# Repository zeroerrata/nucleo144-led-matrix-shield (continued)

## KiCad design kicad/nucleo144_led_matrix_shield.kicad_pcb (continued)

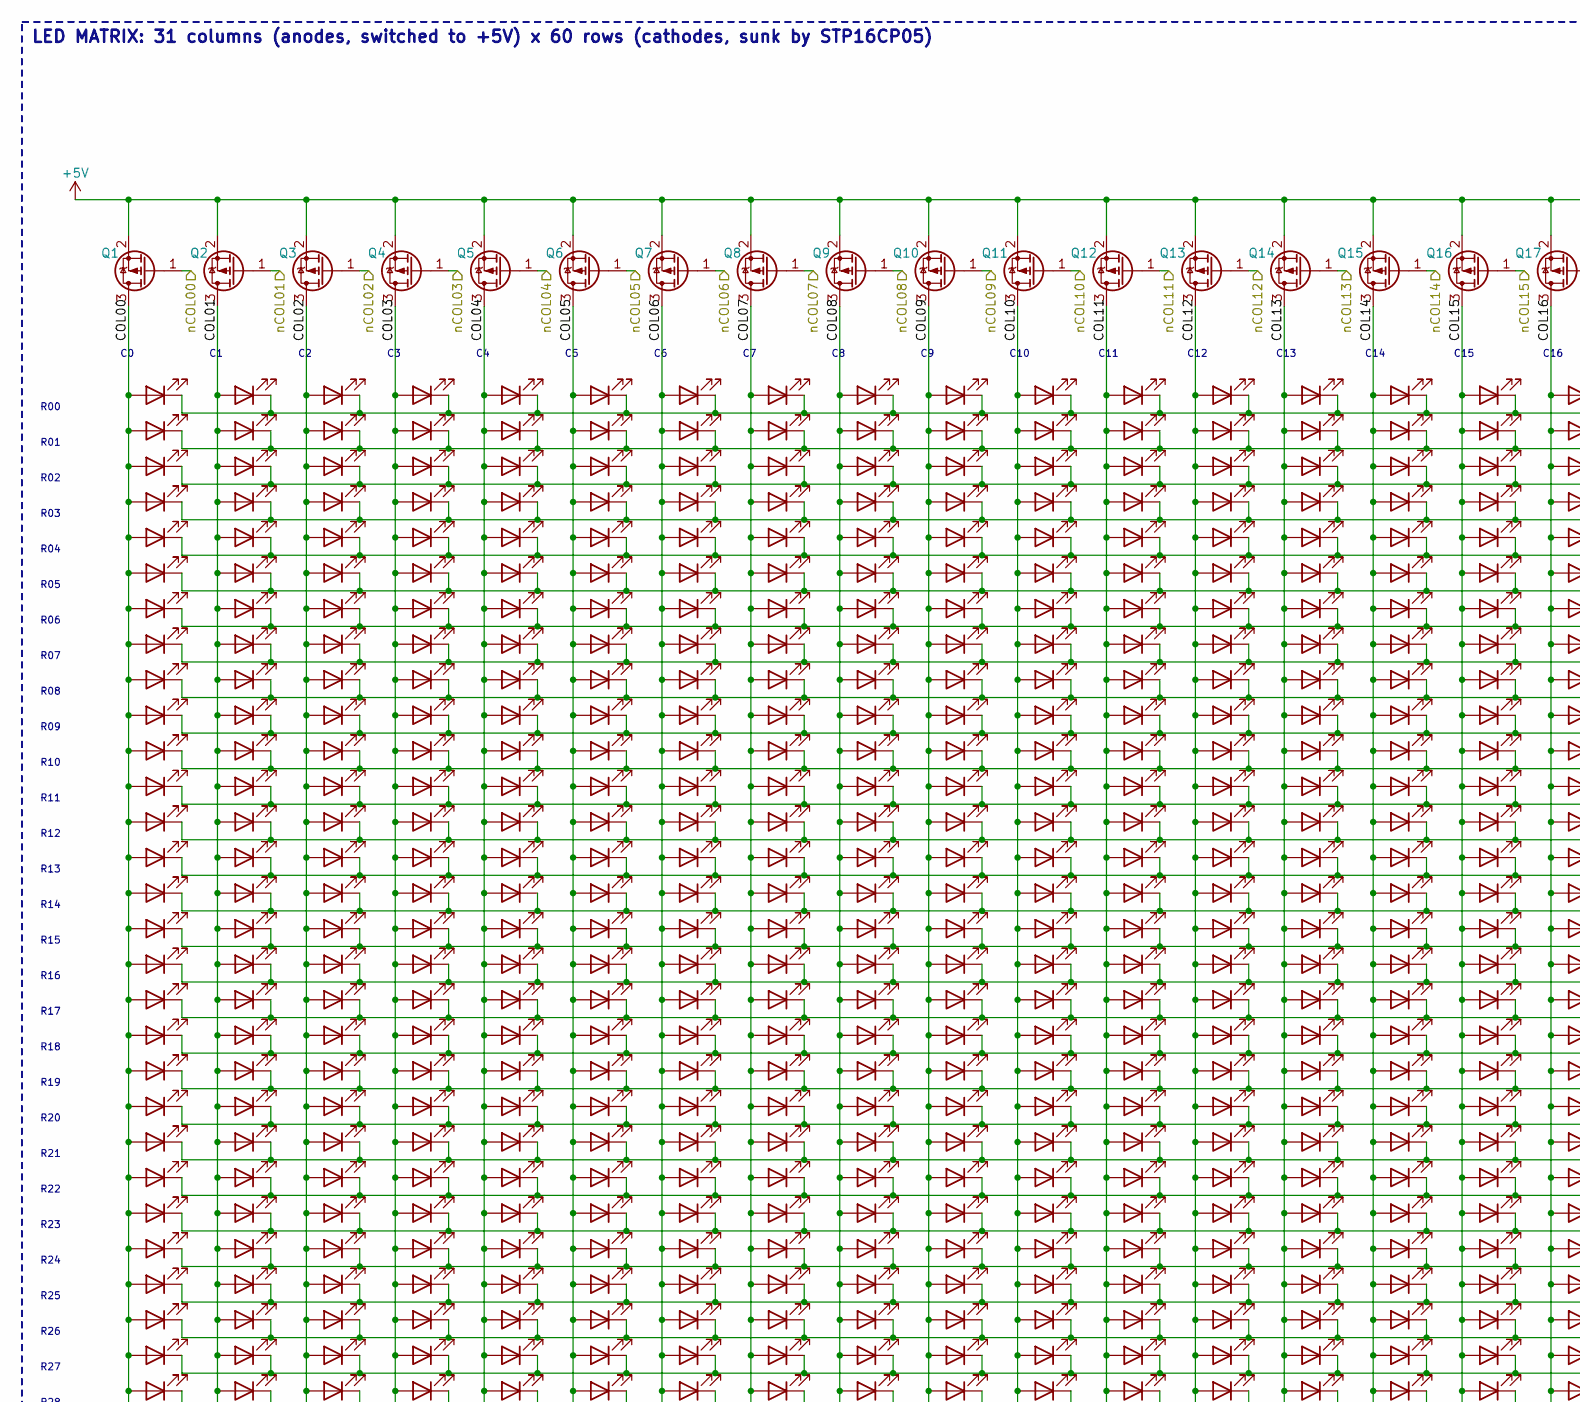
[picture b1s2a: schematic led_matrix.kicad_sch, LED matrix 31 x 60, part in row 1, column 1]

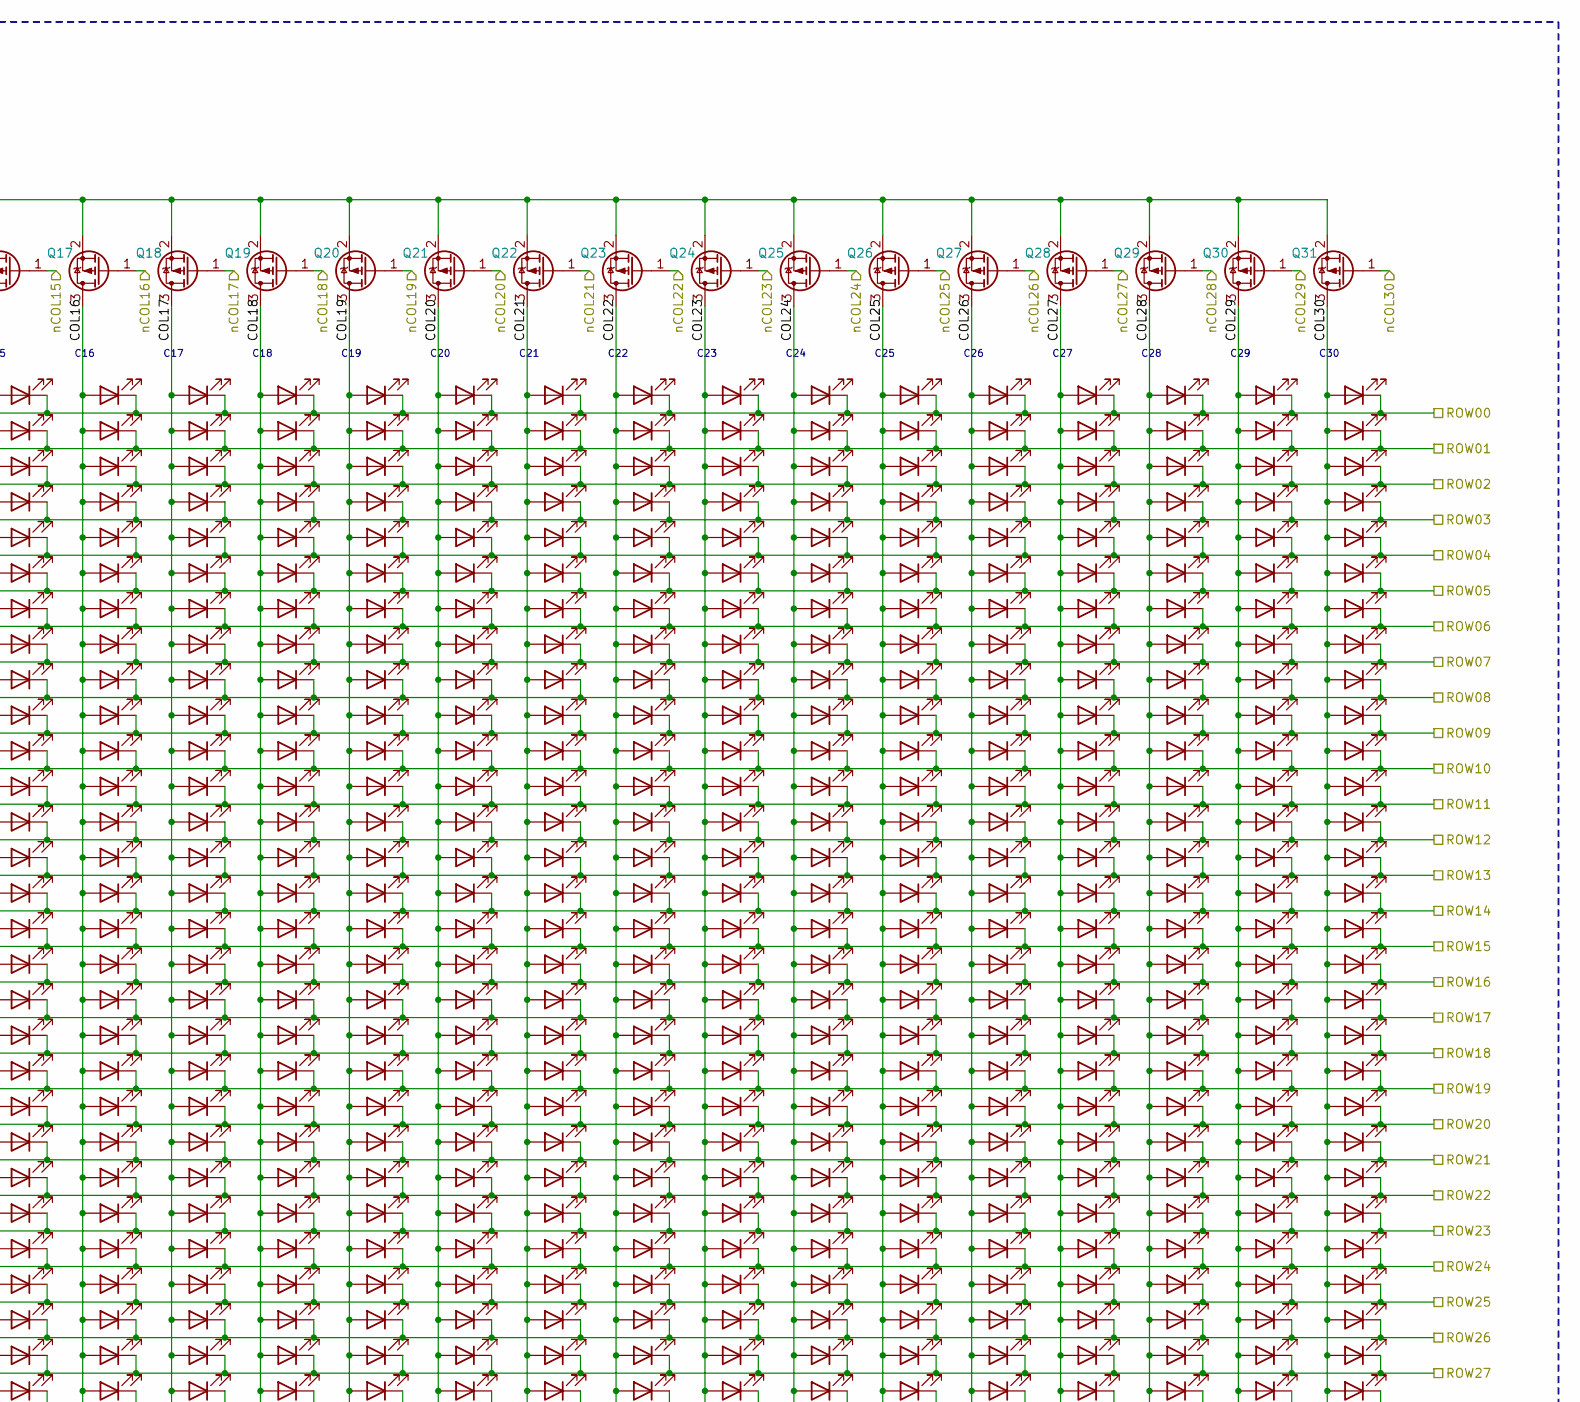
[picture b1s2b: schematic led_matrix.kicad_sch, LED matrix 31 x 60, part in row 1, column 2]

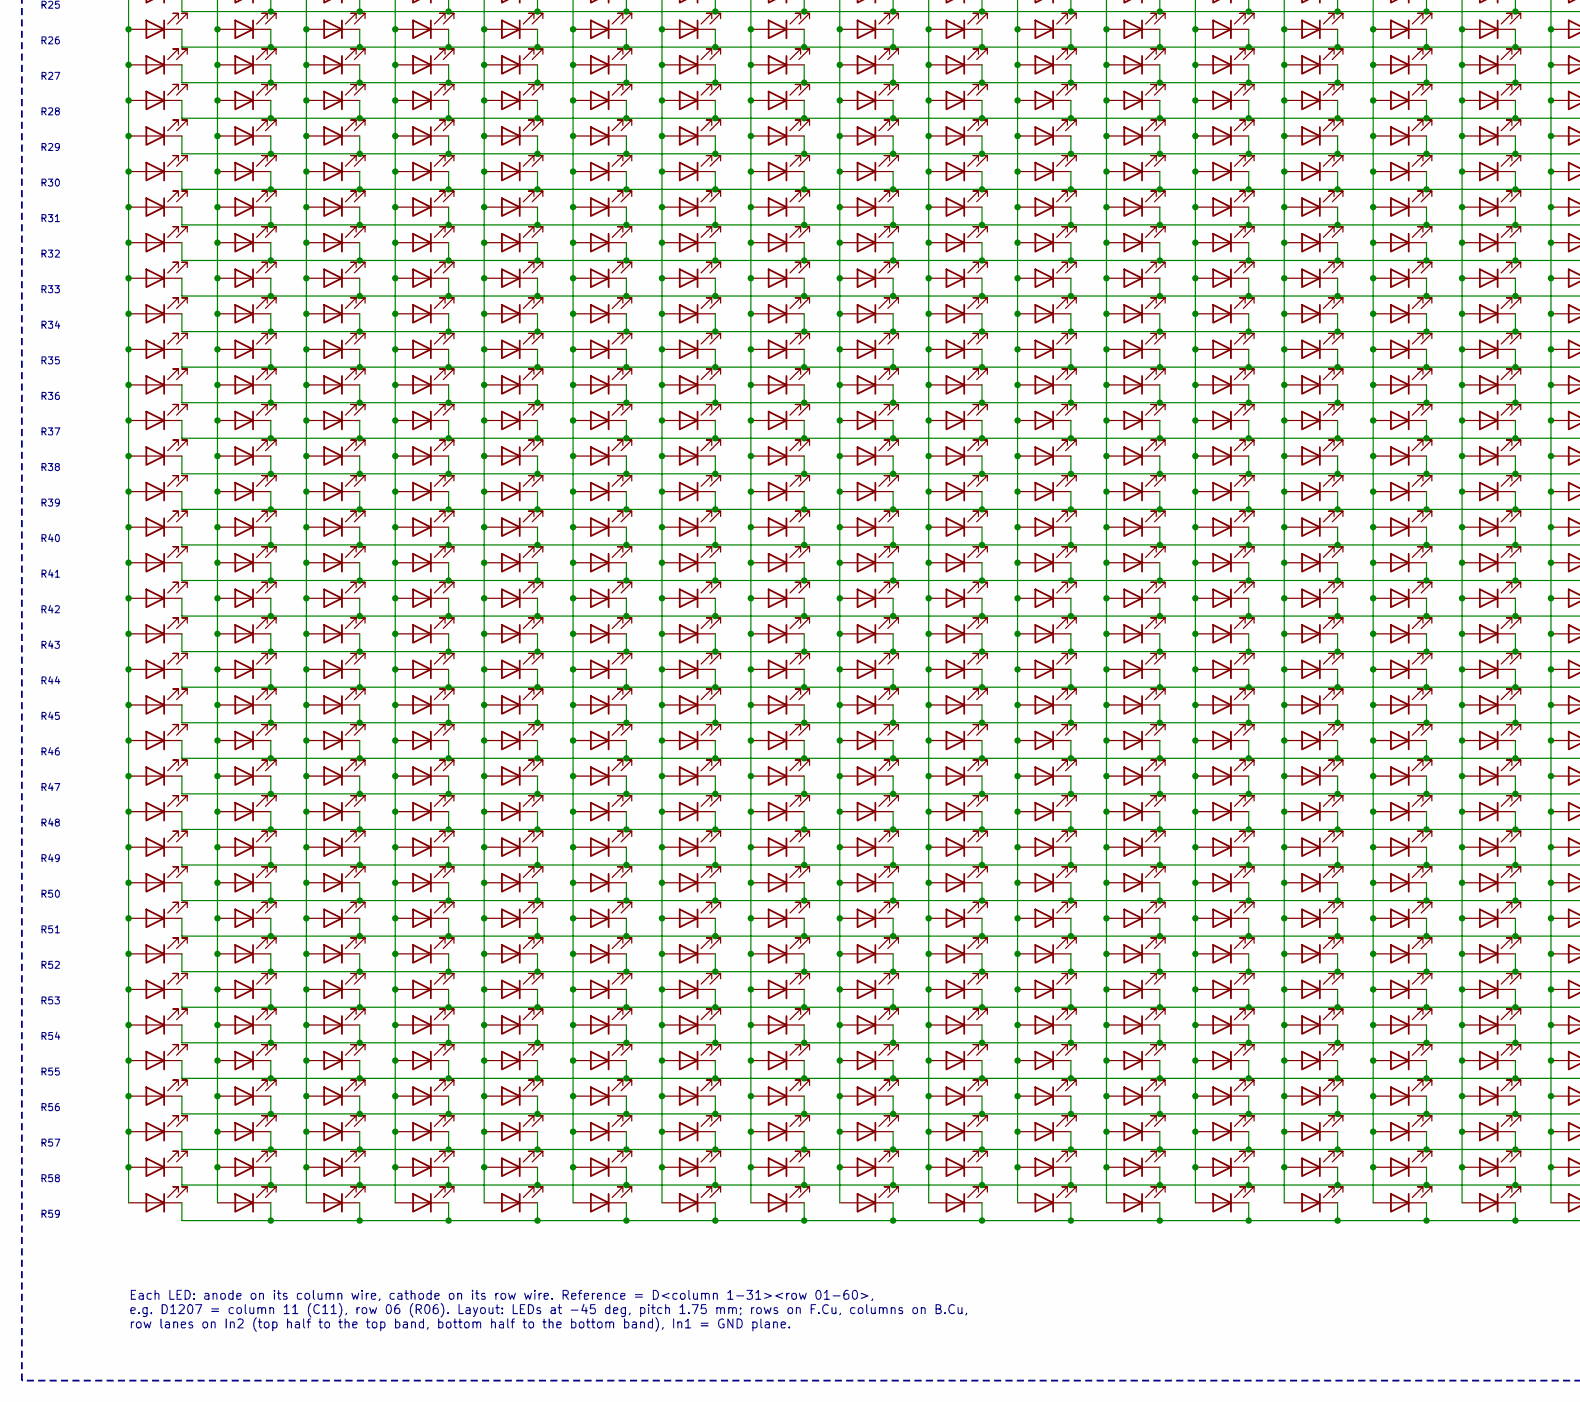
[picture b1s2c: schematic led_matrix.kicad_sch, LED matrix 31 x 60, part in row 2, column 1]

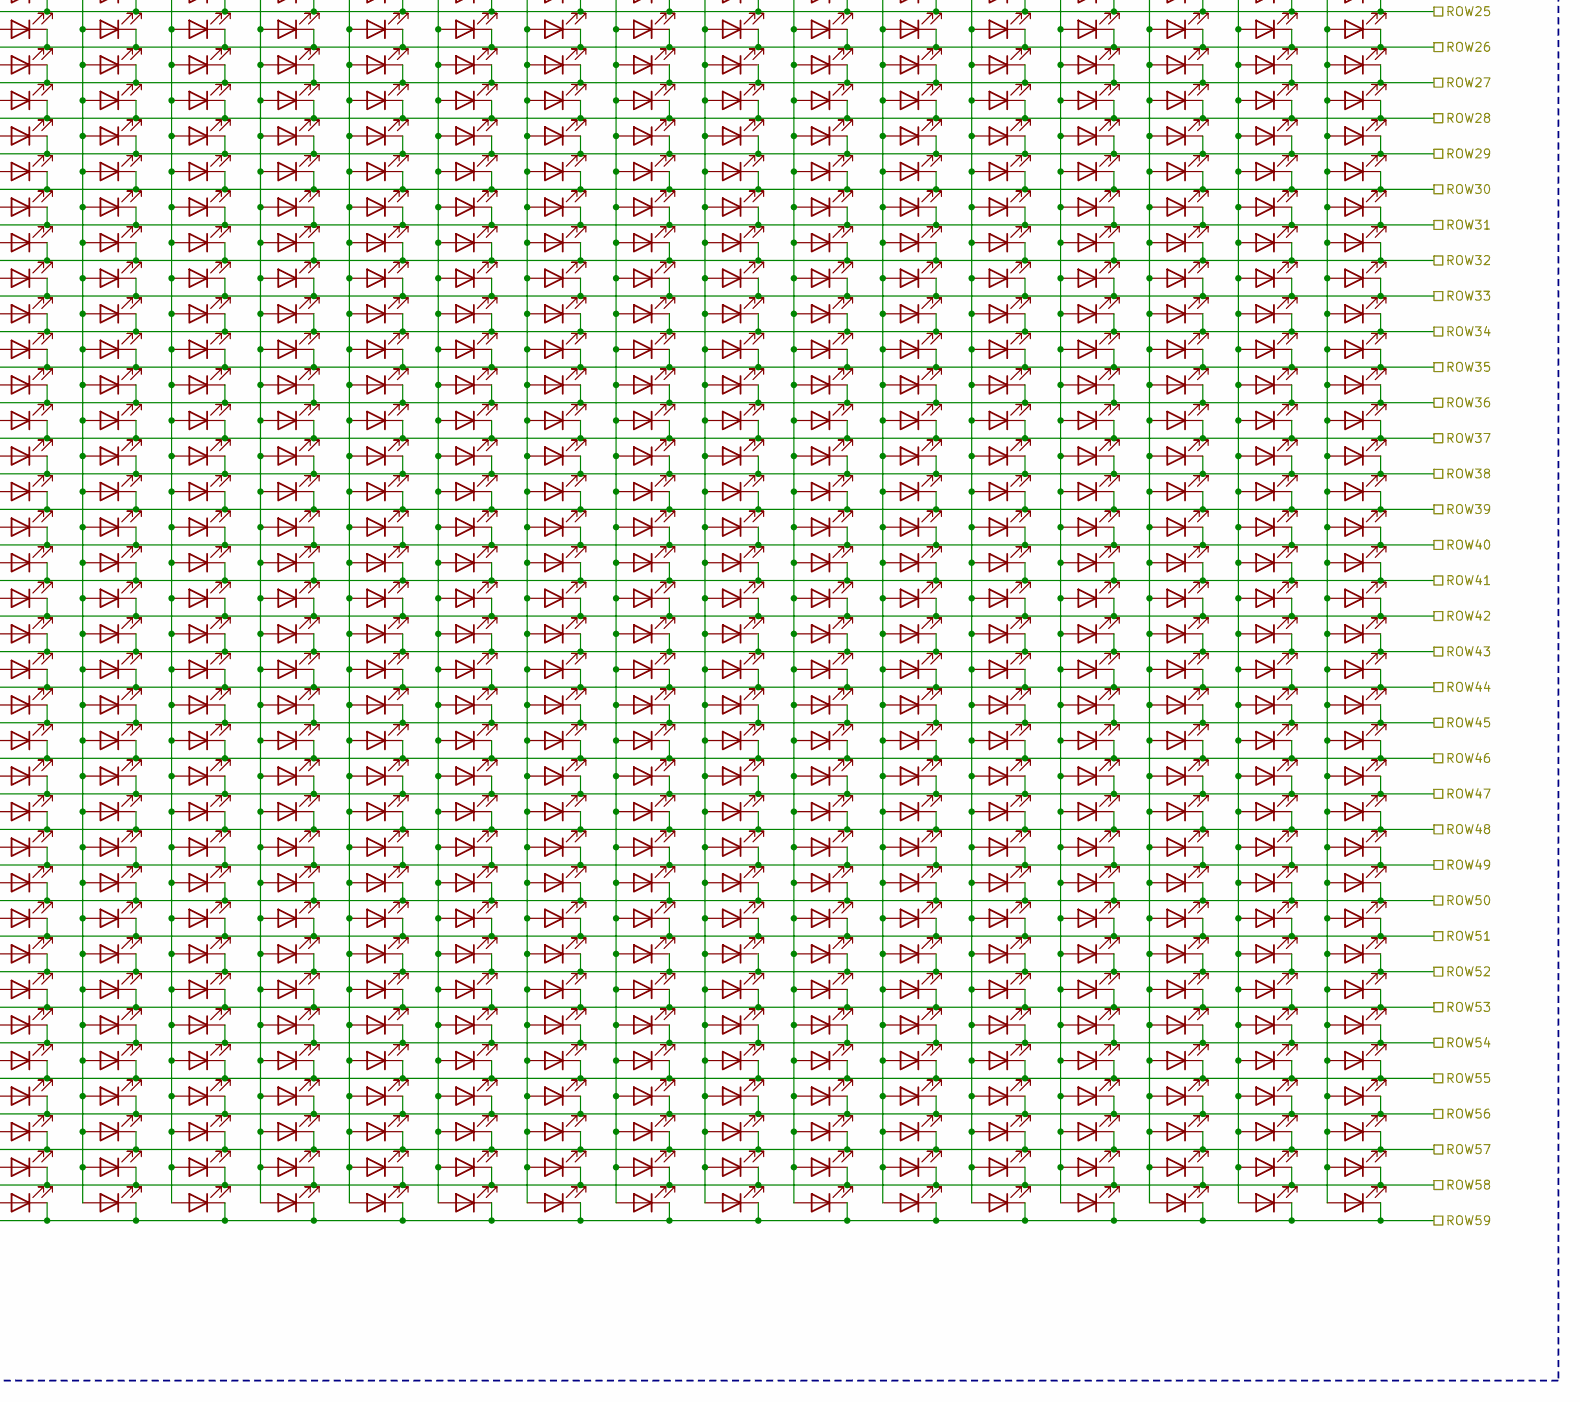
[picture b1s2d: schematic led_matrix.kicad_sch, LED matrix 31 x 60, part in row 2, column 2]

Parts:
D101, D102, D103, D104, D105, D106, D107, D108, D109, D110, D111, D112, D113, D114, D115, D116, D117, D118, D119, D120, D121, D122, D123, D124, D125, D126, D127, D128, D129, D130, D131, D132, D133, D134, D135, D136, D137, D138, D139, D140, D141, D142, D143, D144, D145, D146, D147, D148, D149, D150, D151, D152, D153, D154, D155, D156, D157, D158, D159, D160, D201, D202, D203, D204, D205, D206, D207, D208, D209, D210, D211, D212, D213, D214, D215, D216, D217, D218, D219, D220, D221, D222, D223, D224, D225, D226, D227, D228, D229, D230, D231, D232, D233, D234, D235, D236, D237, D238, D239, D240, D241, D242, D243, D244, D245, D246, D247, D248, D249, D250, D251, D252, D253, D254, D255, D256, D257, D258, D259, D260, D301, D302, D303, D304, D305, D306, D307, D308, D309, D310, D311, D312, D313, D314, D315, D316, D317, D318, D319, D320, D321, D322, D323, D324, D325, D326, D327, D328, D329, D330, D331, D332, D333, D334, D335, D336, D337, D338, D339, D340, D341, D342, D343, D344, D345, D346, D347, D348, D349, D350, D351, D352, D353, D354, D355, D356, D357, D358, D359, D360, D401, D402, D403, D404, D405, D406, D407, D408, D409, D410, D411, D412, D413, D414, D415, D416, D417, D418, D419, D420, D421, D422, D423, D424, D425, D426, D427, D428, D429, D430, D431, D432, D433, D434, D435, D436, D437, D438, D439, D440, D441, D442, D443, D444, D445, D446, D447, D448, D449, D450, D451, D452, D453, D454, D455, D456, D457, D458, D459, D460, D501, D502, D503, D504, D505, D506, D507, D508, D509, D510, D511, D512, D513, D514, D515, D516, D517, D518, D519, D520, D521, D522, D523, D524, D525, D526, D527, D528, D529, D530, D531, D532, D533, D534, D535, D536, D537, D538, D539, D540, D541, D542, D543, D544, D545, D546, D547, D548, D549, D550, D551, D552, D553, D554, D555, D556, D557, D558, D559, D560, D601, D602, D603, D604, D605, D606, D607, D608, D609, D610, D611, D612, D613, D614, D615, D616, D617, D618, D619, D620, D621, D622, D623, D624, D625, D626, D627, D628, D629, D630, D631, D632, D633, D634, D635, D636, D637, D638, D639, D640, D641, D642, D643, D644, D645, D646, D647, D648, D649, D650, D651, D652, D653, D654, D655, D656, D657, D658, D659, D660, D701, D702, D703, D704, D705, D706, D707, D708, D709, D710, D711, D712, D713, D714, D715, D716, D717, D718, D719, D720, D721, D722, D723, D724, D725, D726, D727, D728, D729, D730, D731, D732, D733, D734, D735, D736, D737, D738, D739, D740, D741, D742, D743, D744, D745, D746, D747, D748, D749, D750, D751, D752, D753, D754, D755, D756, D757, D758, D759, D760, D801, D802, D803, D804, D805, D806, D807, D808, D809, D810, D811, D812, D813, D814, D815, D816, D817, D818, D819, D820, D821, D822, D823, D824, D825, D826, D827, D828, D829, D830, D831, D832, D833, D834, D835, D836, D837, D838, D839, D840, D841, D842, D843, D844, D845, D846, D847, D848, D849, D850, D851, D852, D853, D854, D855, D856, D857, D858, D859, D860, D901, D902, D903, D904, D905, D906, D907, D908, D909, D910, D911, D912, D913, D914, D915, D916, D917, D918, D919, D920, D921, D922, D923, D924, D925, D926, D927, D928, D929, D930, D931, D932, D933, D934, D935, D936, D937, D938, D939, D940, D941, D942, D943, D944, D945, D946, D947, D948, D949, D950, D951, D952, D953, D954, D955, D956, D957, D958, D959, D960, D1001, D1002, D1003, D1004, D1005, D1006, D1007, D1008, D1009, D1010, D1011, D1012, D1013, D1014, D1015, D1016, D1017, D1018, D1019, D1020, D1021, D1022, D1023, D1024, D1025, D1026, D1027, D1028, D1029, D1030, D1031, D1032, D1033, D1034, D1035, D1036, D1037, D1038, D1039, D1040, D1041, D1042, D1043, D1044, D1045, D1046, D1047, D1048, D1049, D1050, D1051, D1052, D1053, D1054, D1055, D1056, D1057, D1058, D1059, D1060, D1101, D1102, D1103, D1104, D1105, D1106, D1107, D1108, D1109, D1110, D1111, D1112, D1113, D1114, D1115, D1116, D1117, D1118, D1119, D1120, D1121, D1122, D1123, D1124, D1125, D1126, D1127, D1128, D1129, D1130, D1131, D1132, D1133, D1134, D1135, D1136, D1137, D1138, D1139, D1140, D1141, D1142, D1143, D1144, D1145, D1146, D1147, D1148, D1149, D1150, D1151, D1152, D1153, D1154, D1155, D1156, D1157, D1158, D1159, D1160, D1201, D1202, D1203, D1204, D1205, D1206, D1207, D1208, D1209, D1210, D1211, D1212, D1213, D1214, D1215, D1216, D1217, D1218, D1219, D1220, D1221, D1222, D1223, D1224, D1225, D1226, D1227, D1228, D1229, D1230, D1231, D1232, D1233, D1234, D1235, D1236, D1237, D1238, D1239, D1240, D1241, D1242, D1243, D1244, D1245, D1246, D1247, D1248, D1249, D1250, D1251, D1252, D1253, D1254, D1255, D1256, D1257, D1258, D1259, D1260, D1301, D1302, D1303, D1304, D1305, D1306, D1307, D1308, D1309, D1310, D1311, D1312, D1313, D1314, D1315, D1316, D1317, D1318, D1319, D1320, D1321, D1322, D1323, D1324, D1325, D1326, D1327, D1328, D1329, D1330, D1331, D1332, D1333, D1334, D1335, D1336, D1337, D1338, D1339, D1340, D1341, D1342, D1343, D1344, D1345, D1346, D1347, D1348, D1349, D1350, D1351, D1352, D1353, D1354, D1355, D1356, D1357, D1358, D1359, D1360, D1401, D1402, D1403, D1404, D1405, D1406, D1407, D1408, D1409, D1410, D1411, D1412, D1413, D1414, D1415, D1416, D1417, D1418, D1419, D1420, D1421, D1422, D1423, D1424, D1425, D1426, D1427, D1428, D1429, D1430, D1431, D1432, D1433, D1434, D1435, D1436, D1437, D1438, D1439, D1440, D1441, D1442, D1443, D1444, D1445, D1446, D1447, D1448, D1449, D1450, D1451, D1452, D1453, D1454, D1455, D1456, D1457, D1458, D1459, D1460, D1501, D1502, D1503, D1504, D1505, D1506, D1507, D1508, D1509, D1510, D1511, D1512, D1513, D1514, D1515, D1516, D1517, D1518, D1519, D1520, D1521, D1522, D1523, D1524, D1525, D1526, D1527, D1528, D1529, D1530, D1531, D1532, D1533, D1534, D1535, D1536, D1537, D1538, D1539, D1540, D1541, D1542, D1543, D1544, D1545, D1546, D1547, D1548, D1549, D1550, D1551, D1552, D1553, D1554, D1555, D1556, D1557, D1558, D1559, D1560, D1601, D1602, D1603, D1604, D1605, D1606, D1607, D1608, D1609, D1610, D1611, D1612, D1613, D1614, D1615, D1616, D1617, D1618, D1619, D1620, D1621, D1622, D1623, D1624, D1625, D1626, D1627, D1628, D1629, D1630, D1631, D1632, D1633, D1634, D1635, D1636, D1637, D1638, D1639, D1640, D1641, D1642, D1643, D1644, D1645, D1646, D1647, D1648, D1649, D1650, D1651, D1652, D1653, D1654, D1655, D1656, D1657, D1658, D1659, D1660, D1701, D1702, D1703, D1704, D1705, D1706, D1707, D1708, D1709, D1710, D1711, D1712, D1713, D1714, D1715, D1716, D1717, D1718, D1719, D1720, D1721, D1722, D1723, D1724, D1725, D1726, D1727, D1728, D1729, D1730, D1731, D1732, D1733, D1734, D1735, D1736, D1737, D1738, D1739, D1740, D1741, D1742, D1743, D1744, D1745, D1746, D1747, D1748, D1749, D1750, D1751, D1752, D1753, D1754, D1755, D1756, D1757, D1758, D1759, D1760, D1801, D1802, D1803, D1804, D1805, D1806, D1807, D1808, D1809, D1810, D1811, D1812, D1813, D1814, D1815, D1816, D1817, D1818, D1819, D1820, D1821, D1822, D1823, D1824, D1825, D1826, D1827, D1828, D1829, D1830, D1831, D1832, D1833, D1834, D1835, D1836, D1837, D1838, D1839, D1840, D1841, D1842, D1843, D1844, D1845, D1846, D1847, D1848, D1849, D1850, D1851, D1852, D1853, D1854, D1855, D1856, D1857, D1858, D1859, D1860, D1901, D1902, D1903, D1904, D1905, D1906, D1907, D1908, D1909, D1910, D1911, D1912, D1913, D1914, D1915, D1916, D1917, D1918, D1919, D1920, D1921, D1922, D1923, D1924, D1925, D1926, D1927, D1928, D1929, D1930, D1931, D1932, D1933, D1934, D1935, D1936, D1937, D1938, D1939, D1940, D1941, D1942, D1943, D1944, D1945, D1946, D1947, D1948, D1949, D1950, D1951, D1952, D1953, D1954, D1955, D1956, D1957, D1958, D1959, D1960, D2001, D2002, D2003, D2004, D2005, D2006, D2007, D2008, D2009, D2010, D2011, D2012, D2013, D2014, D2015, D2016, D2017, D2018, D2019, D2020, D2021, D2022, D2023, D2024, D2025, D2026, D2027, D2028, D2029, D2030, D2031, D2032, D2033, D2034, D2035, D2036, D2037, D2038, D2039, D2040, D2041, D2042, D2043, D2044, D2045, D2046, D2047, D2048, D2049, D2050, D2051, D2052, D2053, D2054, D2055, D2056, D2057, D2058, D2059, D2060, D2101, D2102, D2103, D2104, D2105, D2106, D2107, D2108, D2109, D2110, D2111, D2112, D2113, D2114, D2115, D2116, D2117, D2118, D2119, D2120, D2121, D2122, D2123, D2124, D2125, D2126, D2127, D2128, D2129, D2130, D2131, D2132, D2133, D2134, D2135, D2136, D2137, D2138, D2139, D2140, D2141, D2142, D2143, D2144, D2145, D2146, D2147, D2148, D2149, D2150, D2151, D2152, D2153, D2154, D2155, D2156, D2157, D2158, D2159, D2160, D2201, D2202, D2203, D2204, D2205, D2206, D2207, D2208, D2209, D2210, D2211, D2212, D2213, D2214, D2215, D2216, D2217, D2218, D2219, D2220, D2221, D2222, D2223, D2224, D2225, D2226, D2227, D2228, D2229, D2230, D2231, D2232, D2233, D2234, D2235, D2236, D2237, D2238, D2239, D2240, D2241, D2242, D2243, D2244, D2245, D2246, D2247, D2248, D2249, D2250, D2251, D2252, D2253, D2254, D2255, D2256, D2257, D2258, D2259, D2260, D2301, D2302, D2303, D2304, D2305, D2306, D2307, D2308, D2309, D2310, D2311, D2312, D2313, D2314, D2315, D2316, D2317, D2318, D2319, D2320, D2321, D2322, D2323, D2324, D2325, D2326, D2327, D2328, D2329, D2330, D2331, D2332, D2333, D2334, D2335, D2336, D2337, D2338, D2339, D2340, D2341, D2342, D2343, D2344, D2345, D2346, D2347, D2348, D2349, D2350, D2351, D2352, D2353, D2354, D2355, D2356, D2357, D2358, D2359, D2360, D2401, D2402, D2403, D2404, D2405, D2406, D2407, D2408, D2409, D2410, D2411, D2412, D2413, D2414, D2415, D2416, D2417, D2418, D2419, D2420, D2421, D2422, D2423, D2424, D2425, D2426, D2427, D2428, D2429, D2430, D2431, D2432, D2433, D2434, D2435, D2436, D2437, D2438, D2439, D2440, D2441, D2442, D2443, D2444, D2445, D2446, D2447, D2448, D2449, D2450, D2451, D2452, D2453, D2454, D2455, D2456, D2457, D2458, D2459, D2460, D2501, D2502, D2503, D2504, D2505, D2506, D2507, D2508, D2509, D2510, D2511, D2512, D2513, D2514, D2515, D2516, D2517, D2518, D2519, D2520, D2521, D2522, D2523, D2524, D2525, D2526, D2527, D2528, D2529, D2530, D2531, D2532, D2533, D2534, D2535, D2536, D2537, D2538, D2539, D2540, D2541, D2542, D2543, D2544, D2545, D2546, D2547, D2548, D2549, D2550, D2551, D2552, D2553, D2554, D2555, D2556, D2557, D2558, D2559, D2560, D2601, D2602, D2603, D2604, D2605, D2606, D2607, D2608, D2609, D2610, D2611, D2612, D2613, D2614, D2615, D2616, D2617, D2618, D2619, D2620, D2621, D2622, D2623, D2624, D2625, D2626, D2627, D2628, D2629, D2630, D2631, D2632, D2633, D2634, D2635, D2636, D2637, D2638, D2639, D2640, D2641, D2642, D2643, D2644, D2645, D2646, D2647, D2648, D2649, D2650, D2651, D2652, D2653, D2654, D2655, D2656, D2657, D2658, D2659, D2660, D2701, D2702, D2703, D2704, D2705, D2706, D2707, D2708, D2709, D2710, D2711, D2712, D2713, D2714, D2715, D2716, D2717, D2718, D2719, D2720, D2721, D2722, D2723, D2724, D2725, D2726, D2727, D2728, D2729, D2730, D2731, D2732, D2733, D2734, D2735, D2736, D2737, D2738, D2739, D2740, D2741, D2742, D2743, D2744, D2745, D2746, D2747, D2748, D2749, D2750, D2751, D2752, D2753, D2754, D2755, D2756, D2757, D2758, D2759, D2760, D2801, D2802, D2803, D2804, D2805, D2806, D2807, D2808, D2809, D2810, D2811, D2812, D2813, D2814, D2815, D2816, D2817, D2818, D2819, D2820, D2821, D2822, D2823, D2824, D2825, D2826, D2827, D2828, D2829, D2830, D2831, D2832, D2833, D2834, D2835, D2836, D2837, D2838, D2839, D2840, D2841, D2842, D2843, D2844, D2845, D2846, D2847, D2848, D2849, D2850, D2851, D2852, D2853, D2854, D2855, D2856, D2857, D2858, D2859, D2860, D2901, D2902, D2903, D2904, D2905, D2906, D2907, D2908, D2909, D2910, D2911, D2912, D2913, D2914, D2915, D2916, D2917, D2918, D2919, D2920, D2921, D2922, D2923, D2924, D2925, D2926, D2927, D2928, D2929, D2930, D2931, D2932, D2933, D2934, D2935, D2936, D2937, D2938, D2939, D2940, D2941, D2942, D2943, D2944, D2945, D2946, D2947, D2948, D2949, D2950, D2951, D2952, D2953, D2954, D2955, D2956, D2957, D2958, D2959, D2960, D3001, D3002, D3003, D3004, D3005, D3006, D3007, D3008, D3009, D3010, D3011, D3012, D3013, D3014, D3015, D3016, D3017, D3018, D3019, D3020, D3021, D3022, D3023, D3024, D3025, D3026, D3027, D3028, D3029, D3030, D3031, D3032, D3033, D3034, D3035, D3036, D3037, D3038, D3039, D3040, D3041, D3042, D3043, D3044, D3045, D3046, D3047, D3048, D3049, D3050, D3051, D3052, D3053, D3054, D3055, D3056, D3057, D3058, D3059, D3060, D3101, D3102, D3103, D3104, D3105, D3106, D3107, D3108, D3109, D3110, D3111, D3112, D3113, D3114, D3115, D3116, D3117, D3118, D3119, D3120, D3121, D3122, D3123, D3124, D3125, D3126, D3127, D3128, D3129, D3130, D3131, D3132, D3133, D3134, D3135, D3136, D3137, D3138, D3139, D3140, D3141, D3142, D3143, D3144, D3145, D3146, D3147, D3148, D3149, D3150, D3151, D3152, D3153, D3154, D3155, D3156, D3157, D3158, D3159, D3160: red; LED_0402_1005Metric_NoSilk; MPN NCD0402R1; LCSC C130719
Q1, Q2, Q3, Q4, Q5, Q6, Q7, Q8, Q9, Q10, Q11, Q12, Q13, Q14, Q15, Q16, Q17, Q18, Q19, Q20, Q21, Q22, Q23, Q24, Q25, Q26, Q27, Q28, Q29, Q30, Q31: AO3401A; SOT-23; MPN AO3401A; LCSC C15127

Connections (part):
+5V: Q1.2 (S), Q2.2 (S), Q3.2 (S), Q4.2 (S), Q5.2 (S), Q6.2 (S), Q7.2 (S), Q8.2 (S), Q9.2 (S), Q10.2 (S), Q11.2 (S), Q12.2 (S), Q13.2 (S), Q14.2 (S), Q15.2 (S), Q16.2 (S), Q17.2 (S), Q18.2 (S), Q19.2 (S), Q20.2 (S), Q21.2 (S), Q22.2 (S), Q23.2 (S), Q24.2 (S), Q25.2 (S), Q26.2 (S), Q27.2 (S), Q28.2 (S), Q29.2 (S), Q30.2 (S), Q31.2 (S); also elsewhere on the board
/LED matrix/COL00: D101.2 (A), D102.2 (A), D103.2 (A), D104.2 (A), D105.2 (A), D106.2 (A), D107.2 (A), D108.2 (A), D109.2 (A), D110.2 (A), D111.2 (A), D112.2 (A), D113.2 (A), D114.2 (A), D115.2 (A), D116.2 (A), D117.2 (A), D118.2 (A), D119.2 (A), D120.2 (A), D121.2 (A), D122.2 (A), D123.2 (A), D124.2 (A), D125.2 (A), D126.2 (A), D127.2 (A), D128.2 (A), D129.2 (A), D130.2 (A), D131.2 (A), D132.2 (A), D133.2 (A), D134.2 (A), D135.2 (A), D136.2 (A), D137.2 (A), D138.2 (A), D139.2 (A), D140.2 (A), D141.2 (A), D142.2 (A), D143.2 (A), D144.2 (A), D145.2 (A), D146.2 (A), D147.2 (A), D148.2 (A), D149.2 (A), D150.2 (A), D151.2 (A), D152.2 (A), D153.2 (A), D154.2 (A), D155.2 (A), D156.2 (A), D157.2 (A), D158.2 (A), D159.2 (A), D160.2 (A), Q1.3 (D)
/LED matrix/COL01: D201.2 (A), D202.2 (A), D203.2 (A), D204.2 (A), D205.2 (A), D206.2 (A), D207.2 (A), D208.2 (A), D209.2 (A), D210.2 (A), D211.2 (A), D212.2 (A), D213.2 (A), D214.2 (A), D215.2 (A), D216.2 (A), D217.2 (A), D218.2 (A), D219.2 (A), D220.2 (A), D221.2 (A), D222.2 (A), D223.2 (A), D224.2 (A), D225.2 (A), D226.2 (A), D227.2 (A), D228.2 (A), D229.2 (A), D230.2 (A), D231.2 (A), D232.2 (A), D233.2 (A), D234.2 (A), D235.2 (A), D236.2 (A), D237.2 (A), D238.2 (A), D239.2 (A), D240.2 (A), D241.2 (A), D242.2 (A), D243.2 (A), D244.2 (A), D245.2 (A), D246.2 (A), D247.2 (A), D248.2 (A), D249.2 (A), D250.2 (A), D251.2 (A), D252.2 (A), D253.2 (A), D254.2 (A), D255.2 (A), D256.2 (A), D257.2 (A), D258.2 (A), D259.2 (A), D260.2 (A), Q2.3 (D)
/LED matrix/COL02: D301.2 (A), D302.2 (A), D303.2 (A), D304.2 (A), D305.2 (A), D306.2 (A), D307.2 (A), D308.2 (A), D309.2 (A), D310.2 (A), D311.2 (A), D312.2 (A), D313.2 (A), D314.2 (A), D315.2 (A), D316.2 (A), D317.2 (A), D318.2 (A), D319.2 (A), D320.2 (A), D321.2 (A), D322.2 (A), D323.2 (A), D324.2 (A), D325.2 (A), D326.2 (A), D327.2 (A), D328.2 (A), D329.2 (A), D330.2 (A), D331.2 (A), D332.2 (A), D333.2 (A), D334.2 (A), D335.2 (A), D336.2 (A), D337.2 (A), D338.2 (A), D339.2 (A), D340.2 (A), D341.2 (A), D342.2 (A), D343.2 (A), D344.2 (A), D345.2 (A), D346.2 (A), D347.2 (A), D348.2 (A), D349.2 (A), D350.2 (A), D351.2 (A), D352.2 (A), D353.2 (A), D354.2 (A), D355.2 (A), D356.2 (A), D357.2 (A), D358.2 (A), D359.2 (A), D360.2 (A), Q3.3 (D)
/LED matrix/COL03: D401.2 (A), D402.2 (A), D403.2 (A), D404.2 (A), D405.2 (A), D406.2 (A), D407.2 (A), D408.2 (A), D409.2 (A), D410.2 (A), D411.2 (A), D412.2 (A), D413.2 (A), D414.2 (A), D415.2 (A), D416.2 (A), D417.2 (A), D418.2 (A), D419.2 (A), D420.2 (A), D421.2 (A), D422.2 (A), D423.2 (A), D424.2 (A), D425.2 (A), D426.2 (A), D427.2 (A), D428.2 (A), D429.2 (A), D430.2 (A), D431.2 (A), D432.2 (A), D433.2 (A), D434.2 (A), D435.2 (A), D436.2 (A), D437.2 (A), D438.2 (A), D439.2 (A), D440.2 (A), D441.2 (A), D442.2 (A), D443.2 (A), D444.2 (A), D445.2 (A), D446.2 (A), D447.2 (A), D448.2 (A), D449.2 (A), D450.2 (A), D451.2 (A), D452.2 (A), D453.2 (A), D454.2 (A), D455.2 (A), D456.2 (A), D457.2 (A), D458.2 (A), D459.2 (A), D460.2 (A), Q4.3 (D)
/LED matrix/COL04: D501.2 (A), D502.2 (A), D503.2 (A), D504.2 (A), D505.2 (A), D506.2 (A), D507.2 (A), D508.2 (A), D509.2 (A), D510.2 (A), D511.2 (A), D512.2 (A), D513.2 (A), D514.2 (A), D515.2 (A), D516.2 (A), D517.2 (A), D518.2 (A), D519.2 (A), D520.2 (A), D521.2 (A), D522.2 (A), D523.2 (A), D524.2 (A), D525.2 (A), D526.2 (A), D527.2 (A), D528.2 (A), D529.2 (A), D530.2 (A), D531.2 (A), D532.2 (A), D533.2 (A), D534.2 (A), D535.2 (A), D536.2 (A), D537.2 (A), D538.2 (A), D539.2 (A), D540.2 (A), D541.2 (A), D542.2 (A), D543.2 (A), D544.2 (A), D545.2 (A), D546.2 (A), D547.2 (A), D548.2 (A), D549.2 (A), D550.2 (A), D551.2 (A), D552.2 (A), D553.2 (A), D554.2 (A), D555.2 (A), D556.2 (A), D557.2 (A), D558.2 (A), D559.2 (A), D560.2 (A), Q5.3 (D)
/LED matrix/COL05: D601.2 (A), D602.2 (A), D603.2 (A), D604.2 (A), D605.2 (A), D606.2 (A), D607.2 (A), D608.2 (A), D609.2 (A), D610.2 (A), D611.2 (A), D612.2 (A), D613.2 (A), D614.2 (A), D615.2 (A), D616.2 (A), D617.2 (A), D618.2 (A), D619.2 (A), D620.2 (A), D621.2 (A), D622.2 (A), D623.2 (A), D624.2 (A), D625.2 (A), D626.2 (A), D627.2 (A), D628.2 (A), D629.2 (A), D630.2 (A), D631.2 (A), D632.2 (A), D633.2 (A), D634.2 (A), D635.2 (A), D636.2 (A), D637.2 (A), D638.2 (A), D639.2 (A), D640.2 (A), D641.2 (A), D642.2 (A), D643.2 (A), D644.2 (A), D645.2 (A), D646.2 (A), D647.2 (A), D648.2 (A), D649.2 (A), D650.2 (A), D651.2 (A), D652.2 (A), D653.2 (A), D654.2 (A), D655.2 (A), D656.2 (A), D657.2 (A), D658.2 (A), D659.2 (A), D660.2 (A), Q6.3 (D)
/LED matrix/COL06: D701.2 (A), D702.2 (A), D703.2 (A), D704.2 (A), D705.2 (A), D706.2 (A), D707.2 (A), D708.2 (A), D709.2 (A), D710.2 (A), D711.2 (A), D712.2 (A), D713.2 (A), D714.2 (A), D715.2 (A), D716.2 (A), D717.2 (A), D718.2 (A), D719.2 (A), D720.2 (A), D721.2 (A), D722.2 (A), D723.2 (A), D724.2 (A), D725.2 (A), D726.2 (A), D727.2 (A), D728.2 (A), D729.2 (A), D730.2 (A), D731.2 (A), D732.2 (A), D733.2 (A), D734.2 (A), D735.2 (A), D736.2 (A), D737.2 (A), D738.2 (A), D739.2 (A), D740.2 (A), D741.2 (A), D742.2 (A), D743.2 (A), D744.2 (A), D745.2 (A), D746.2 (A), D747.2 (A), D748.2 (A), D749.2 (A), D750.2 (A), D751.2 (A), D752.2 (A), D753.2 (A), D754.2 (A), D755.2 (A), D756.2 (A), D757.2 (A), D758.2 (A), D759.2 (A), D760.2 (A), Q7.3 (D)
/LED matrix/COL07: D801.2 (A), D802.2 (A), D803.2 (A), D804.2 (A), D805.2 (A), D806.2 (A), D807.2 (A), D808.2 (A), D809.2 (A), D810.2 (A), D811.2 (A), D812.2 (A), D813.2 (A), D814.2 (A), D815.2 (A), D816.2 (A), D817.2 (A), D818.2 (A), D819.2 (A), D820.2 (A), D821.2 (A), D822.2 (A), D823.2 (A), D824.2 (A), D825.2 (A), D826.2 (A), D827.2 (A), D828.2 (A), D829.2 (A), D830.2 (A), D831.2 (A), D832.2 (A), D833.2 (A), D834.2 (A), D835.2 (A), D836.2 (A), D837.2 (A), D838.2 (A), D839.2 (A), D840.2 (A), D841.2 (A), D842.2 (A), D843.2 (A), D844.2 (A), D845.2 (A), D846.2 (A), D847.2 (A), D848.2 (A), D849.2 (A), D850.2 (A), D851.2 (A), D852.2 (A), D853.2 (A), D854.2 (A), D855.2 (A), D856.2 (A), D857.2 (A), D858.2 (A), D859.2 (A), D860.2 (A), Q8.3 (D)
/LED matrix/COL08: D901.2 (A), D902.2 (A), D903.2 (A), D904.2 (A), D905.2 (A), D906.2 (A), D907.2 (A), D908.2 (A), D909.2 (A), D910.2 (A), D911.2 (A), D912.2 (A), D913.2 (A), D914.2 (A), D915.2 (A), D916.2 (A), D917.2 (A), D918.2 (A), D919.2 (A), D920.2 (A), D921.2 (A), D922.2 (A), D923.2 (A), D924.2 (A), D925.2 (A), D926.2 (A), D927.2 (A), D928.2 (A), D929.2 (A), D930.2 (A), D931.2 (A), D932.2 (A), D933.2 (A), D934.2 (A), D935.2 (A), D936.2 (A), D937.2 (A), D938.2 (A), D939.2 (A), D940.2 (A), D941.2 (A), D942.2 (A), D943.2 (A), D944.2 (A), D945.2 (A), D946.2 (A), D947.2 (A), D948.2 (A), D949.2 (A), D950.2 (A), D951.2 (A), D952.2 (A), D953.2 (A), D954.2 (A), D955.2 (A), D956.2 (A), D957.2 (A), D958.2 (A), D959.2 (A), D960.2 (A), Q9.3 (D)
/LED matrix/COL09: D1001.2 (A), D1002.2 (A), D1003.2 (A), D1004.2 (A), D1005.2 (A), D1006.2 (A), D1007.2 (A), D1008.2 (A), D1009.2 (A), D1010.2 (A), D1011.2 (A), D1012.2 (A), D1013.2 (A), D1014.2 (A), D1015.2 (A), D1016.2 (A), D1017.2 (A), D1018.2 (A), D1019.2 (A), D1020.2 (A), D1021.2 (A), D1022.2 (A), D1023.2 (A), D1024.2 (A), D1025.2 (A), D1026.2 (A), D1027.2 (A), D1028.2 (A), D1029.2 (A), D1030.2 (A), D1031.2 (A), D1032.2 (A), D1033.2 (A), D1034.2 (A), D1035.2 (A), D1036.2 (A), D1037.2 (A), D1038.2 (A), D1039.2 (A), D1040.2 (A), D1041.2 (A), D1042.2 (A), D1043.2 (A), D1044.2 (A), D1045.2 (A), D1046.2 (A), D1047.2 (A), D1048.2 (A), D1049.2 (A), D1050.2 (A), D1051.2 (A), D1052.2 (A), D1053.2 (A), D1054.2 (A), D1055.2 (A), D1056.2 (A), D1057.2 (A), D1058.2 (A), D1059.2 (A), D1060.2 (A), Q10.3 (D)
/LED matrix/COL10: D1101.2 (A), D1102.2 (A), D1103.2 (A), D1104.2 (A), D1105.2 (A), D1106.2 (A), D1107.2 (A), D1108.2 (A), D1109.2 (A), D1110.2 (A), D1111.2 (A), D1112.2 (A), D1113.2 (A), D1114.2 (A), D1115.2 (A), D1116.2 (A), D1117.2 (A), D1118.2 (A), D1119.2 (A), D1120.2 (A), D1121.2 (A), D1122.2 (A), D1123.2 (A), D1124.2 (A), D1125.2 (A), D1126.2 (A), D1127.2 (A), D1128.2 (A), D1129.2 (A), D1130.2 (A), D1131.2 (A), D1132.2 (A), D1133.2 (A), D1134.2 (A), D1135.2 (A), D1136.2 (A), D1137.2 (A), D1138.2 (A), D1139.2 (A), D1140.2 (A), D1141.2 (A), D1142.2 (A), D1143.2 (A), D1144.2 (A), D1145.2 (A), D1146.2 (A), D1147.2 (A), D1148.2 (A), D1149.2 (A), D1150.2 (A), D1151.2 (A), D1152.2 (A), D1153.2 (A), D1154.2 (A), D1155.2 (A), D1156.2 (A), D1157.2 (A), D1158.2 (A), D1159.2 (A), D1160.2 (A), Q11.3 (D)
/LED matrix/COL11: D1201.2 (A), D1202.2 (A), D1203.2 (A), D1204.2 (A), D1205.2 (A), D1206.2 (A), D1207.2 (A), D1208.2 (A), D1209.2 (A), D1210.2 (A), D1211.2 (A), D1212.2 (A), D1213.2 (A), D1214.2 (A), D1215.2 (A), D1216.2 (A), D1217.2 (A), D1218.2 (A), D1219.2 (A), D1220.2 (A), D1221.2 (A), D1222.2 (A), D1223.2 (A), D1224.2 (A), D1225.2 (A), D1226.2 (A), D1227.2 (A), D1228.2 (A), D1229.2 (A), D1230.2 (A), D1231.2 (A), D1232.2 (A), D1233.2 (A), D1234.2 (A), D1235.2 (A), D1236.2 (A), D1237.2 (A), D1238.2 (A), D1239.2 (A), D1240.2 (A), D1241.2 (A), D1242.2 (A), D1243.2 (A), D1244.2 (A), D1245.2 (A), D1246.2 (A), D1247.2 (A), D1248.2 (A), D1249.2 (A), D1250.2 (A), D1251.2 (A), D1252.2 (A), D1253.2 (A), D1254.2 (A), D1255.2 (A), D1256.2 (A), D1257.2 (A), D1258.2 (A), D1259.2 (A), D1260.2 (A), Q12.3 (D)
/LED matrix/COL12: D1301.2 (A), D1302.2 (A), D1303.2 (A), D1304.2 (A), D1305.2 (A), D1306.2 (A), D1307.2 (A), D1308.2 (A), D1309.2 (A), D1310.2 (A), D1311.2 (A), D1312.2 (A), D1313.2 (A), D1314.2 (A), D1315.2 (A), D1316.2 (A), D1317.2 (A), D1318.2 (A), D1319.2 (A), D1320.2 (A), D1321.2 (A), D1322.2 (A), D1323.2 (A), D1324.2 (A), D1325.2 (A), D1326.2 (A), D1327.2 (A), D1328.2 (A), D1329.2 (A), D1330.2 (A), D1331.2 (A), D1332.2 (A), D1333.2 (A), D1334.2 (A), D1335.2 (A), D1336.2 (A), D1337.2 (A), D1338.2 (A), D1339.2 (A), D1340.2 (A), D1341.2 (A), D1342.2 (A), D1343.2 (A), D1344.2 (A), D1345.2 (A), D1346.2 (A), D1347.2 (A), D1348.2 (A), D1349.2 (A), D1350.2 (A), D1351.2 (A), D1352.2 (A), D1353.2 (A), D1354.2 (A), D1355.2 (A), D1356.2 (A), D1357.2 (A), D1358.2 (A), D1359.2 (A), D1360.2 (A), Q13.3 (D)
/LED matrix/COL13: D1401.2 (A), D1402.2 (A), D1403.2 (A), D1404.2 (A), D1405.2 (A), D1406.2 (A), D1407.2 (A), D1408.2 (A), D1409.2 (A), D1410.2 (A), D1411.2 (A), D1412.2 (A), D1413.2 (A), D1414.2 (A), D1415.2 (A), D1416.2 (A), D1417.2 (A), D1418.2 (A), D1419.2 (A), D1420.2 (A), D1421.2 (A), D1422.2 (A), D1423.2 (A), D1424.2 (A), D1425.2 (A), D1426.2 (A), D1427.2 (A), D1428.2 (A), D1429.2 (A), D1430.2 (A), D1431.2 (A), D1432.2 (A), D1433.2 (A), D1434.2 (A), D1435.2 (A), D1436.2 (A), D1437.2 (A), D1438.2 (A), D1439.2 (A), D1440.2 (A), D1441.2 (A), D1442.2 (A), D1443.2 (A), D1444.2 (A), D1445.2 (A), D1446.2 (A), D1447.2 (A), D1448.2 (A), D1449.2 (A), D1450.2 (A), D1451.2 (A), D1452.2 (A), D1453.2 (A), D1454.2 (A), D1455.2 (A), D1456.2 (A), D1457.2 (A), D1458.2 (A), D1459.2 (A), D1460.2 (A), Q14.3 (D)
/LED matrix/COL14: D1501.2 (A), D1502.2 (A), D1503.2 (A), D1504.2 (A), D1505.2 (A), D1506.2 (A), D1507.2 (A), D1508.2 (A), D1509.2 (A), D1510.2 (A), D1511.2 (A), D1512.2 (A), D1513.2 (A), D1514.2 (A), D1515.2 (A), D1516.2 (A), D1517.2 (A), D1518.2 (A), D1519.2 (A), D1520.2 (A), D1521.2 (A), D1522.2 (A), D1523.2 (A), D1524.2 (A), D1525.2 (A), D1526.2 (A), D1527.2 (A), D1528.2 (A), D1529.2 (A), D1530.2 (A), D1531.2 (A), D1532.2 (A), D1533.2 (A), D1534.2 (A), D1535.2 (A), D1536.2 (A), D1537.2 (A), D1538.2 (A), D1539.2 (A), D1540.2 (A), D1541.2 (A), D1542.2 (A), D1543.2 (A), D1544.2 (A), D1545.2 (A), D1546.2 (A), D1547.2 (A), D1548.2 (A), D1549.2 (A), D1550.2 (A), D1551.2 (A), D1552.2 (A), D1553.2 (A), D1554.2 (A), D1555.2 (A), D1556.2 (A), D1557.2 (A), D1558.2 (A), D1559.2 (A), D1560.2 (A), Q15.3 (D)
/LED matrix/COL15: D1601.2 (A), D1602.2 (A), D1603.2 (A), D1604.2 (A), D1605.2 (A), D1606.2 (A), D1607.2 (A), D1608.2 (A), D1609.2 (A), D1610.2 (A), D1611.2 (A), D1612.2 (A), D1613.2 (A), D1614.2 (A), D1615.2 (A), D1616.2 (A), D1617.2 (A), D1618.2 (A), D1619.2 (A), D1620.2 (A), D1621.2 (A), D1622.2 (A), D1623.2 (A), D1624.2 (A), D1625.2 (A), D1626.2 (A), D1627.2 (A), D1628.2 (A), D1629.2 (A), D1630.2 (A), D1631.2 (A), D1632.2 (A), D1633.2 (A), D1634.2 (A), D1635.2 (A), D1636.2 (A), D1637.2 (A), D1638.2 (A), D1639.2 (A), D1640.2 (A), D1641.2 (A), D1642.2 (A), D1643.2 (A), D1644.2 (A), D1645.2 (A), D1646.2 (A), D1647.2 (A), D1648.2 (A), D1649.2 (A), D1650.2 (A), D1651.2 (A), D1652.2 (A), D1653.2 (A), D1654.2 (A), D1655.2 (A), D1656.2 (A), D1657.2 (A), D1658.2 (A), D1659.2 (A), D1660.2 (A), Q16.3 (D)
/LED matrix/COL16: D1701.2 (A), D1702.2 (A), D1703.2 (A), D1704.2 (A), D1705.2 (A), D1706.2 (A), D1707.2 (A), D1708.2 (A), D1709.2 (A), D1710.2 (A), D1711.2 (A), D1712.2 (A), D1713.2 (A), D1714.2 (A), D1715.2 (A), D1716.2 (A), D1717.2 (A), D1718.2 (A), D1719.2 (A), D1720.2 (A), D1721.2 (A), D1722.2 (A), D1723.2 (A), D1724.2 (A), D1725.2 (A), D1726.2 (A), D1727.2 (A), D1728.2 (A), D1729.2 (A), D1730.2 (A), D1731.2 (A), D1732.2 (A), D1733.2 (A), D1734.2 (A), D1735.2 (A), D1736.2 (A), D1737.2 (A), D1738.2 (A), D1739.2 (A), D1740.2 (A), D1741.2 (A), D1742.2 (A), D1743.2 (A), D1744.2 (A), D1745.2 (A), D1746.2 (A), D1747.2 (A), D1748.2 (A), D1749.2 (A), D1750.2 (A), D1751.2 (A), D1752.2 (A), D1753.2 (A), D1754.2 (A), D1755.2 (A), D1756.2 (A), D1757.2 (A), D1758.2 (A), D1759.2 (A), D1760.2 (A), Q17.3 (D)
/LED matrix/COL17: D1801.2 (A), D1802.2 (A), D1803.2 (A), D1804.2 (A), D1805.2 (A), D1806.2 (A), D1807.2 (A), D1808.2 (A), D1809.2 (A), D1810.2 (A), D1811.2 (A), D1812.2 (A), D1813.2 (A), D1814.2 (A), D1815.2 (A), D1816.2 (A), D1817.2 (A), D1818.2 (A), D1819.2 (A), D1820.2 (A), D1821.2 (A), D1822.2 (A), D1823.2 (A), D1824.2 (A), D1825.2 (A), D1826.2 (A), D1827.2 (A), D1828.2 (A), D1829.2 (A), D1830.2 (A), D1831.2 (A), D1832.2 (A), D1833.2 (A), D1834.2 (A), D1835.2 (A), D1836.2 (A), D1837.2 (A), D1838.2 (A), D1839.2 (A), D1840.2 (A), D1841.2 (A), D1842.2 (A), D1843.2 (A), D1844.2 (A), D1845.2 (A), D1846.2 (A), D1847.2 (A), D1848.2 (A), D1849.2 (A), D1850.2 (A), D1851.2 (A), D1852.2 (A), D1853.2 (A), D1854.2 (A), D1855.2 (A), D1856.2 (A), D1857.2 (A), D1858.2 (A), D1859.2 (A), D1860.2 (A), Q18.3 (D)
/LED matrix/COL18: D1901.2 (A), D1902.2 (A), D1903.2 (A), D1904.2 (A), D1905.2 (A), D1906.2 (A), D1907.2 (A), D1908.2 (A), D1909.2 (A), D1910.2 (A), D1911.2 (A), D1912.2 (A), D1913.2 (A), D1914.2 (A), D1915.2 (A), D1916.2 (A), D1917.2 (A), D1918.2 (A), D1919.2 (A), D1920.2 (A), D1921.2 (A), D1922.2 (A), D1923.2 (A), D1924.2 (A), D1925.2 (A), D1926.2 (A), D1927.2 (A), D1928.2 (A), D1929.2 (A), D1930.2 (A), D1931.2 (A), D1932.2 (A), D1933.2 (A), D1934.2 (A), D1935.2 (A), D1936.2 (A), D1937.2 (A), D1938.2 (A), D1939.2 (A), D1940.2 (A), D1941.2 (A), D1942.2 (A), D1943.2 (A), D1944.2 (A), D1945.2 (A), D1946.2 (A), D1947.2 (A), D1948.2 (A), D1949.2 (A), D1950.2 (A), D1951.2 (A), D1952.2 (A), D1953.2 (A), D1954.2 (A), D1955.2 (A), D1956.2 (A), D1957.2 (A), D1958.2 (A), D1959.2 (A), D1960.2 (A), Q19.3 (D)
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
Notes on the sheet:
LED MATRIX: 31 columns (anodes, switched to +5V) x 60 rows (cathodes, sunk by STP16CP05)
C10
C11
C12
C13
C14
C15
C16
C17
C18
C19
C20
C21
C22
C23
C24
C25
C26
C27
C28
C29
C30
R00
R01
R02
R03
R04
R05
R06
R07
R08
R09
R10
R11
R12
R13
R14
R15
R16
R17
